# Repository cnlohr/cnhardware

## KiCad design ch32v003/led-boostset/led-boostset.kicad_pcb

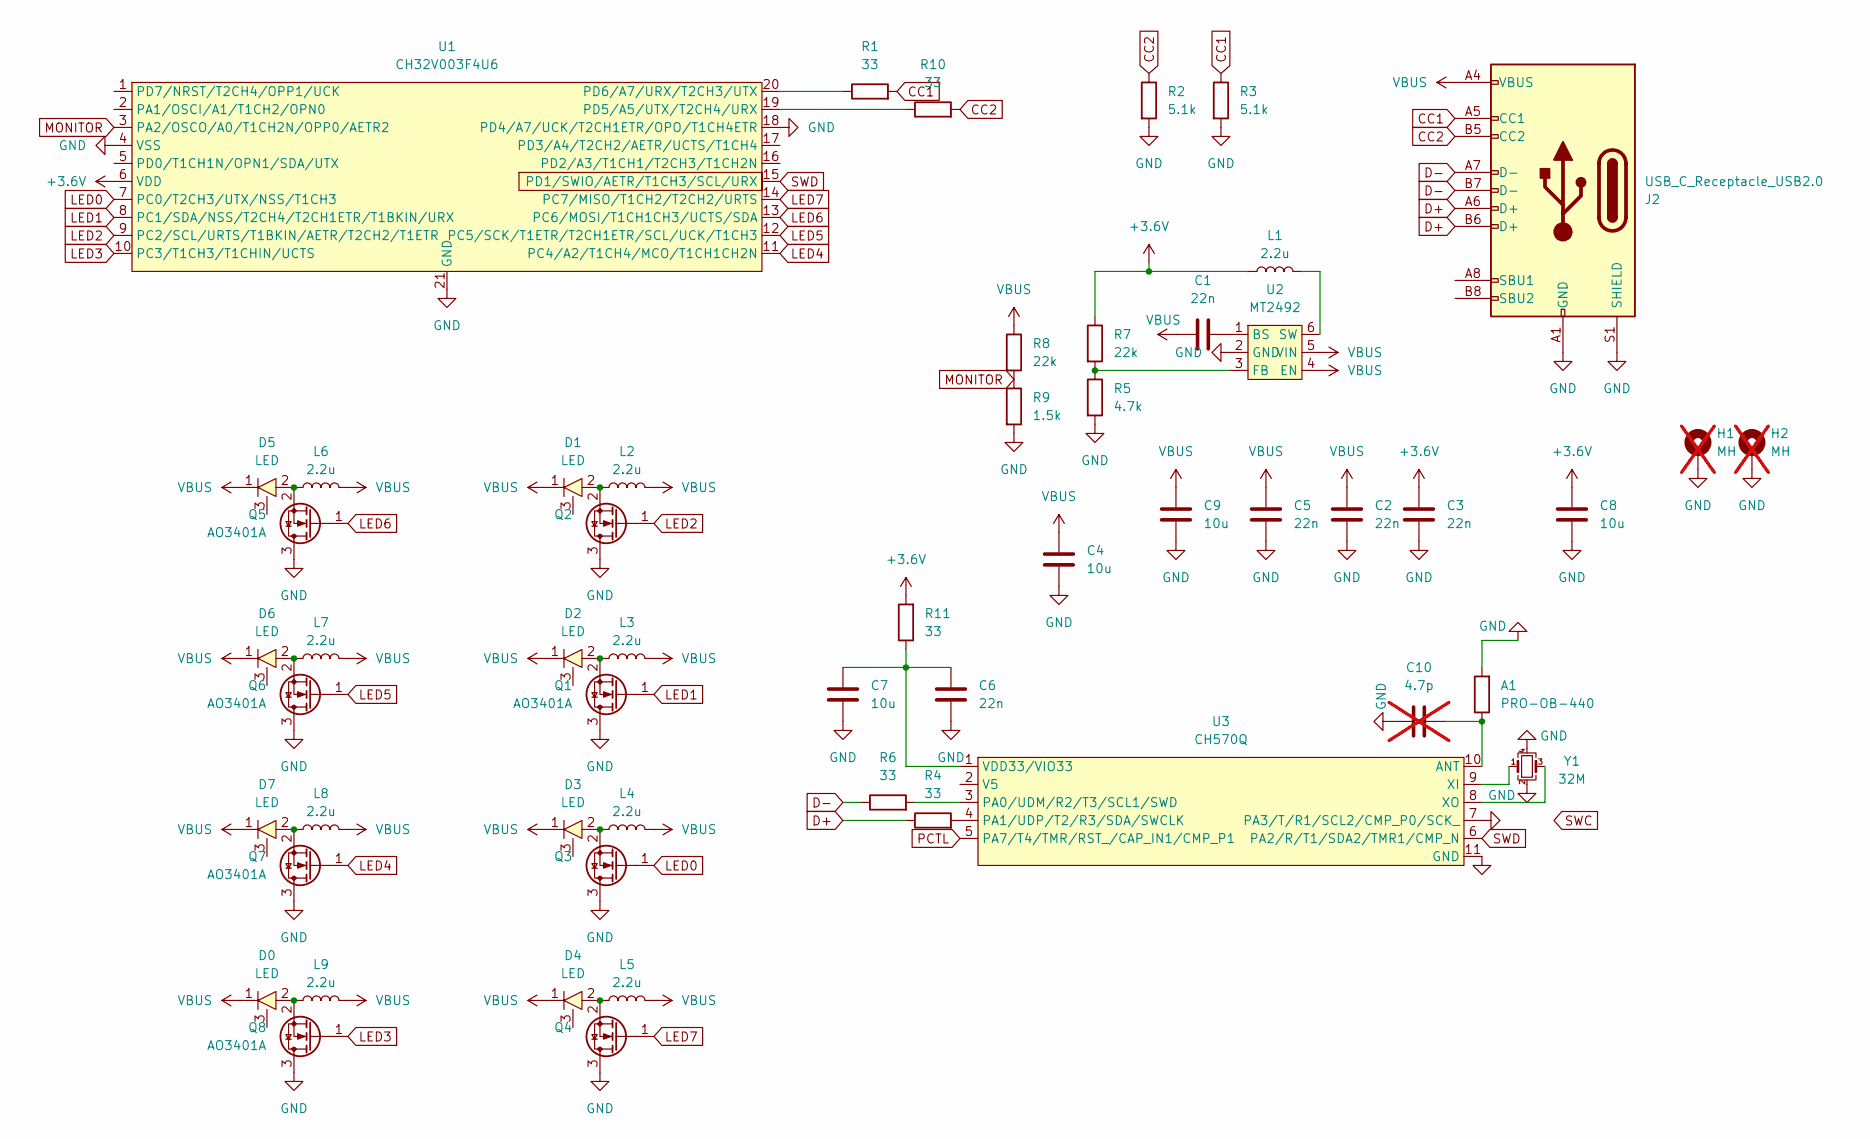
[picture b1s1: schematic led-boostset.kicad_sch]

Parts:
A1: PRO-OB-440; Abracon_PRO-OB-440; LCSC C5122736
C1, C2, C3, C5, C6: 22n; C_0402_1005Metric; LCSC C1532
C4, C7, C8, C9: 10u; C_0805_2012Metric; LCSC C15850
C10: 4.7p; C_0402_1005Metric; not fitted
D0, D1, D2, D3, D4, D5, D6, D7: LED; LED_3535_3W_W_PAD
H1, H2: MH; MountingHole_3.2mm_M3_ISO7380_Pad; not fitted
J2: USB_C_Receptacle_USB2.0; USB_C_SMT_ONLY_Receptacle_USB2.0; LCSC C2927040
L1, L2, L3, L4, L5, L6, L7, L8, L9: 2.2u; L_1008_2520Metric; LCSC C49340356
Q1, Q2, Q3, Q4, Q5, Q6, Q7, Q8: AO3401A; SOT-23; LCSC C15127
R1, R4, R6, R10, R11: 33; R_0603_1608Metric; LCSC C23140
R2, R3: 5.1k; R_0402_1005Metric; LCSC C25905
R5: 4.7k; R_0402_1005Metric; LCSC C25900
R7, R8: 22k; R_0603_1608Metric; LCSC C31850
R9: 1.5k; R_0402_1005Metric; LCSC C25867
U1: CH32V003F4U6; QFN-20-1EP_3x3mm_P0.4mm_EP1.65x1.65mm; LCSC C5299908
U2: MT2492; SOT-23-6; LCSC C89358
U3: CH570Q; DFN-10-1EP_3x3mm_P0.5mm_EP1.7x2.5mm; LCSC C49260680
Y1: 32M; Crystal_SMD_2016-4Pin_2.0x1.6mm; LCSC C718072

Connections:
+3.6V: C3.2, C8.2, L1.1, R7.1, R11.2, U1.6 (VDD)
CC1: J2.A5 (CC1), R1.2, R3.1
CC2: J2.B5 (CC2), R2.1, R10.2
D+: J2.A6 (D+), J2.B6 (D+), R4.1
D-: J2.A7 (D-), J2.B7 (D-), R6.1
GND: A1.2, C2.1, C3.1, C4.1, C5.1, C6.1, C7.1, C8.1, C9.1, C10.2, H1.1, H2.1, J2.A1 (GND), J2.A12 (GND), J2.B1 (GND), J2.B12 (GND), J2.S1 (SHIELD), Q1.3 (D), Q2.3 (D), Q3.3 (D), Q4.3 (D), Q5.3 (D), Q6.3 (D), Q7.3 (D), Q8.3 (D), R2.2, R3.2, R5.2, R9.2, U1.4 (VSS), U1.18 (PD4/A7/UCK/T2CH1ETR/OPO/T1CH4ETR), U1.21 (GND), U2.2 (GND), U3.7 (PA3/T/R1/SCL2/CMP_P0/SCK_), U3.11 (GND), Y1.2, Y1.4
LED0: Q3.1 (G), U1.7 (PC0/T2CH3/UTX/NSS/T1CH3)
LED1: Q1.1 (G), U1.8 (PC1/SDA/NSS/T2CH4/T2CH1ETR/T1BKIN/URX)
LED2: Q2.1 (G), U1.9 (PC2/SCL/URTS/T1BKIN/AETR/T2CH2/T1ETR)
LED3: Q8.1 (G), U1.10 (PC3/T1CH3/T1CHIN/UCTS)
LED4: Q7.1 (G), U1.11 (PC4/A2/T1CH4/MCO/T1CH1CH2N)
LED5: Q6.1 (G), U1.12 (PC5/SCK/T1ETR/T2CH1ETR/SCL/UCK/T1CH3)
LED6: Q5.1 (G), U1.13 (PC6/MOSI/T1CH1CH3/UCTS/SDA)
LED7: Q4.1 (G), U1.14 (PC7/MISO/T1CH2/T2CH2/URTS)
MONITOR: R8.2, R9.1, U1.3 (PA2/OSCO/A0/T1CH2N/OPP0/AETR2)
unnamed: D2.2, L3.1, Q1.2 (S)
unnamed: D1.2, L2.1, Q2.2 (S)
unnamed: D3.2, L4.1, Q3.2 (S)
unnamed: D4.2, L5.1, Q4.2 (S)
unnamed: D5.2, L6.1, Q5.2 (S)
unnamed: D6.2, L7.1, Q6.2 (S)
unnamed: D7.2, L8.1, Q7.2 (S)
unnamed: D0.2, L9.1, Q8.2 (S)
unnamed: R10.1, U1.19 (PD5/A5/UTX/T2CH4/URX)
unnamed: R1.1, U1.20 (PD6/A7/URX/T2CH3/UTX)
unnamed: C1.2, U2.1 (BS)
unnamed: R5.1, R7.2, U2.3 (FB)
unnamed: L1.2, U2.6 (SW)
unnamed: A1.1, C10.1, U3.10 (ANT)
unnamed: R6.2, U3.3 (PA0/UDM/R2/T3/SCL1/SWD)
unnamed: R4.2, U3.4 (PA1/UDP/T2/R3/SDA/SWCLK)
unnamed: C6.2, C7.2, R11.1, U3.1 (VDD33/VIO33)
unnamed: U3.9 (XI), Y1.1
unnamed: U3.8 (XO), Y1.3
PCTL: U3.5 (PA7/T4/TMR/RST_/CAP_IN1/CMP_P1)
SWD: U1.15 (PD1/SWIO/AETR/T1CH3/SCL/URX), U3.6 (PA2/R/T1/SDA2/TMR1/CMP_N)
VBUS: C1.1, C2.2, C4.2, C5.2, C9.2, D0.1, D1.1, D2.1, D3.1, D4.1, D5.1, D6.1, D7.1, J2.A4 (VBUS), J2.A9 (VBUS), J2.B4 (VBUS), J2.B9 (VBUS), L2.2, L3.2, L4.2, L5.2, L6.2, L7.2, L8.2, L9.2, R8.1, U2.4 (EN), U2.5 (VIN)

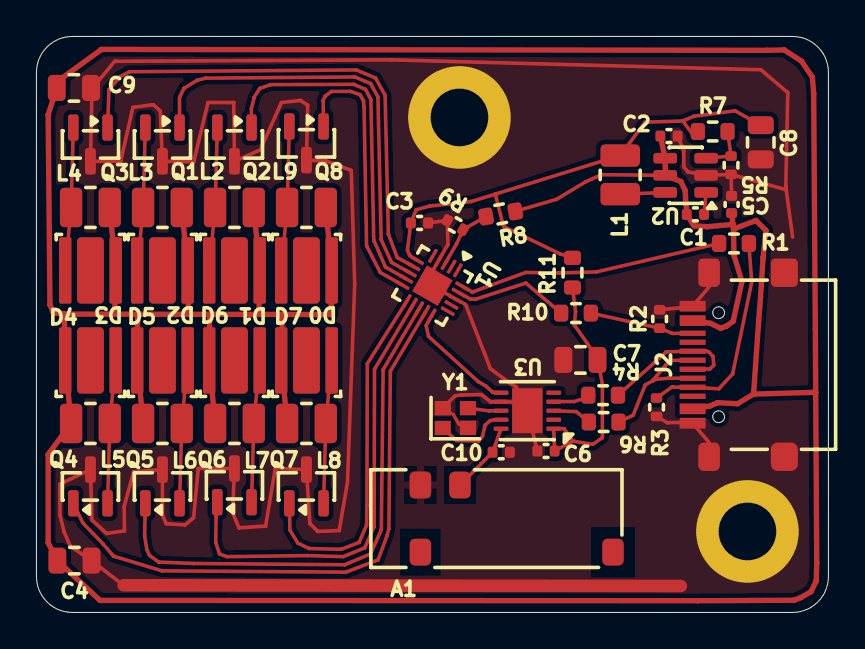
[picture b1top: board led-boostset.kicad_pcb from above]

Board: 2 copper layers, 44.0 x 32.0 mm, 54 parts (0 on the bottom side), 36 nets.

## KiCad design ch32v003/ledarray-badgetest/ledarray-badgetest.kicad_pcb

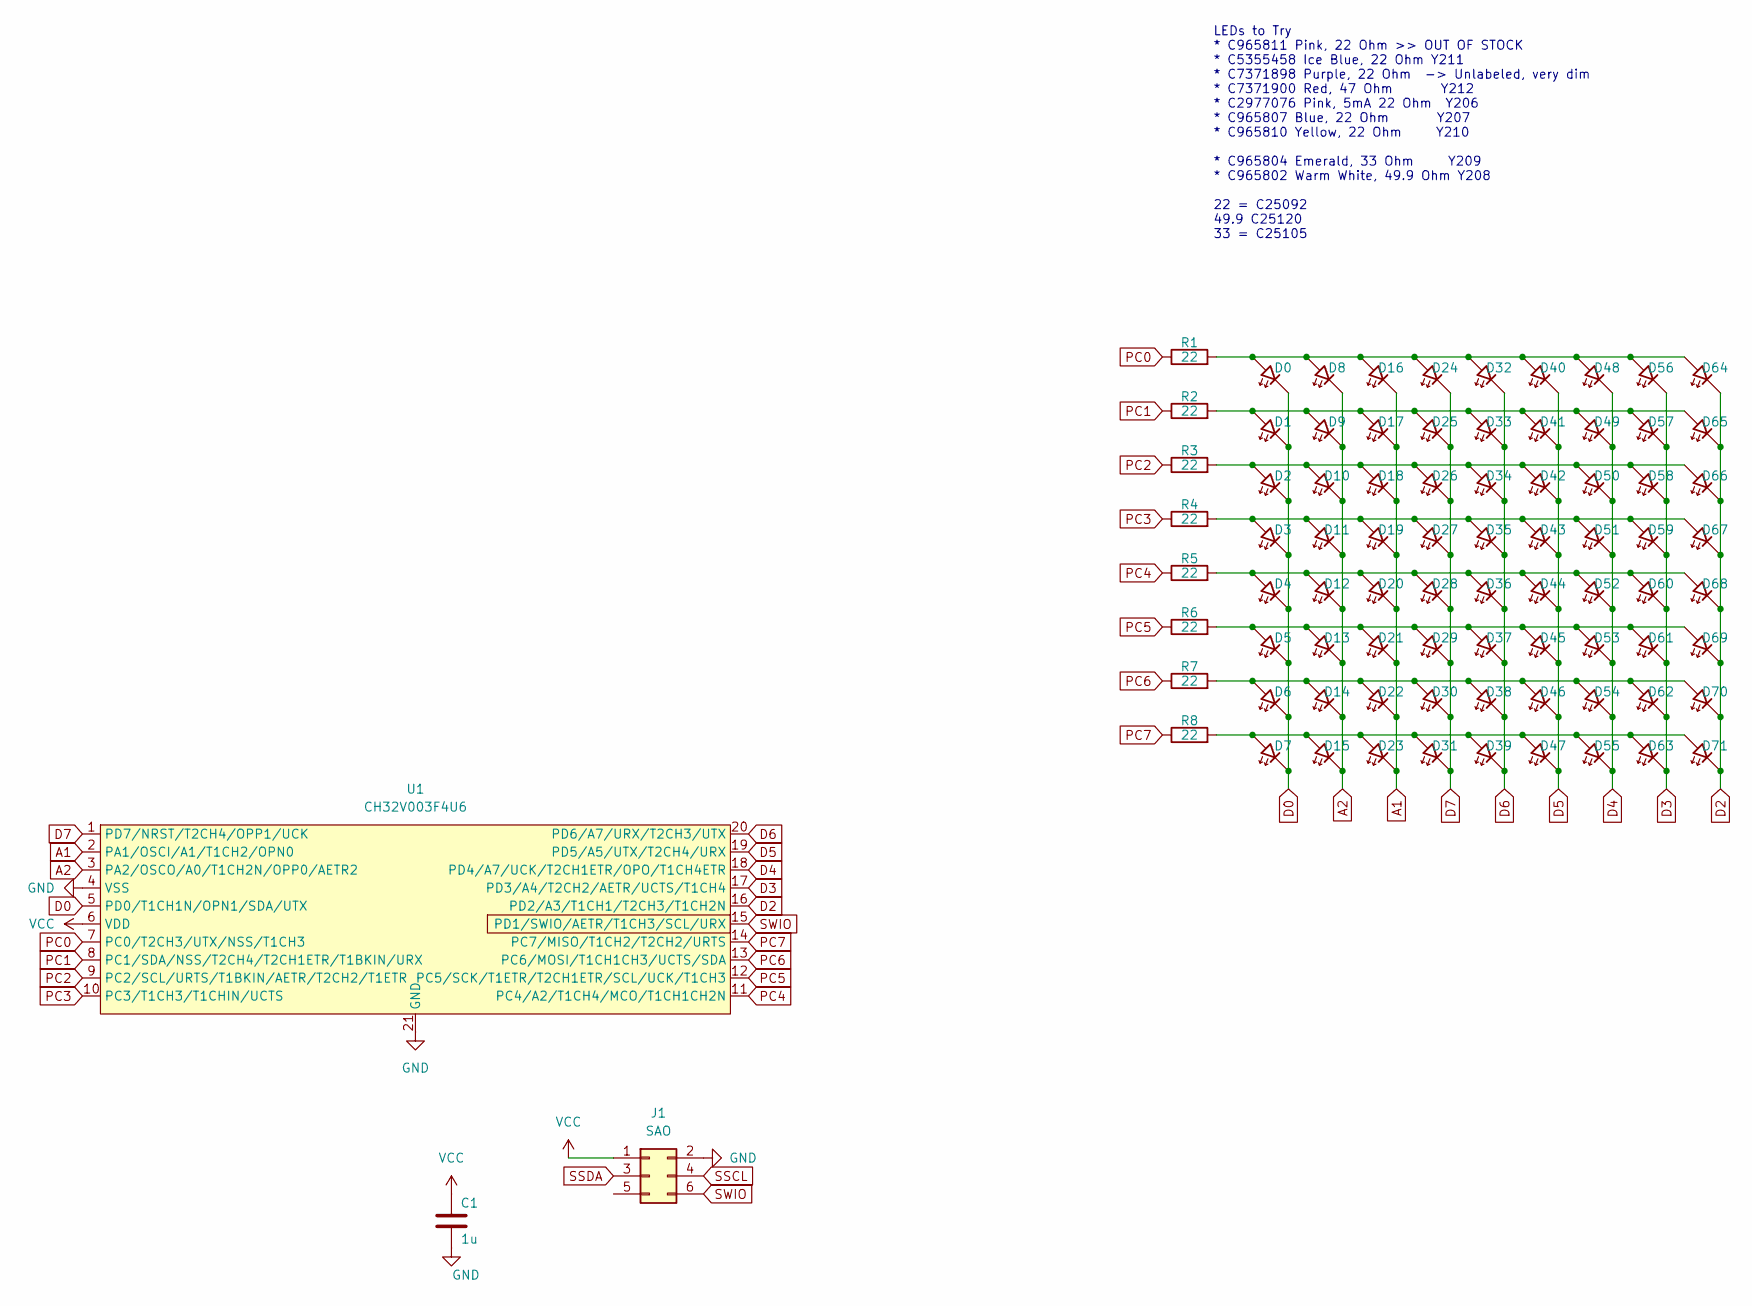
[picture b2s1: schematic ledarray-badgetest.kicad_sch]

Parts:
C1: 1u; R_0402_1005Metric; LCSC C52923
D0, D1, D2, D3, D4, D5, D6, D7, D8, D9, D10, D11, D12, D13, D14, D15, D16, D17, D18, D19, D20, D21, D22, D23, D24, D25, D26, D27, D28, D29, D30, D31, D32, D33, D34, D35, D36, D37, D38, D39, D40, D41, D42, D43, D44, D45, D46, D47, D48, D49, D50, D51, D52, D53, D54, D55, D56, D57, D58, D59, D60, D61, D62, D63, D64, D65, D66, D67, D68, D69, D70, D71: LED_45deg; LED_0603_1608Metric; LCSC C2977076
J1: SAO; PinHeader_2x03_P2.54mm_Vertical_SMD
R1, R2, R3, R4, R5, R6, R7, R8: 22; R_0402_1005Metric; LCSC C25092
U1: CH32V003F4U6; QFN-20-1EP_3x3mm_P0.4mm_EP1.65x1.65mm; LCSC C5299908

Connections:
A1: D16.1 (K), D17.1 (K), D18.1 (K), D19.1 (K), D20.1 (K), D21.1 (K), D22.1 (K), D23.1 (K), U1.2 (PA1/OSCI/A1/T1CH2/OPN0)
A2: D8.1 (K), D9.1 (K), D10.1 (K), D11.1 (K), D12.1 (K), D13.1 (K), D14.1 (K), D15.1 (K), U1.3 (PA2/OSCO/A0/T1CH2N/OPP0/AETR2)
D0: D0.1 (K), D1.1 (K), D2.1 (K), D3.1 (K), D4.1 (K), D5.1 (K), D6.1 (K), D7.1 (K), U1.5 (PD0/T1CH1N/OPN1/SDA/UTX)
D2: D64.1 (K), D65.1 (K), D66.1 (K), D67.1 (K), D68.1 (K), D69.1 (K), D70.1 (K), D71.1 (K), U1.16 (PD2/A3/T1CH1/T2CH3/T1CH2N)
D3: D56.1 (K), D57.1 (K), D58.1 (K), D59.1 (K), D60.1 (K), D61.1 (K), D62.1 (K), D63.1 (K), U1.17 (PD3/A4/T2CH2/AETR/UCTS/T1CH4)
D4: D48.1 (K), D49.1 (K), D50.1 (K), D51.1 (K), D52.1 (K), D53.1 (K), D54.1 (K), D55.1 (K), U1.18 (PD4/A7/UCK/T2CH1ETR/OPO/T1CH4ETR)
D5: D40.1 (K), D41.1 (K), D42.1 (K), D43.1 (K), D44.1 (K), D45.1 (K), D46.1 (K), D47.1 (K), U1.19 (PD5/A5/UTX/T2CH4/URX)
D6: D32.1 (K), D33.1 (K), D34.1 (K), D35.1 (K), D36.1 (K), D37.1 (K), D38.1 (K), D39.1 (K), U1.20 (PD6/A7/URX/T2CH3/UTX)
D7: D24.1 (K), D25.1 (K), D26.1 (K), D27.1 (K), D28.1 (K), D29.1 (K), D30.1 (K), D31.1 (K), U1.1 (PD7/NRST/T2CH4/OPP1/UCK)
GND: C1.1, J1.2, U1.4 (VSS), U1.21 (GND)
unnamed: D0.2 (A), D8.2 (A), D16.2 (A), D24.2 (A), D32.2 (A), D40.2 (A), D48.2 (A), D56.2 (A), D64.2 (A), R1.2
unnamed: D1.2 (A), D9.2 (A), D17.2 (A), D25.2 (A), D33.2 (A), D41.2 (A), D49.2 (A), D57.2 (A), D65.2 (A), R2.2
unnamed: D2.2 (A), D10.2 (A), D18.2 (A), D26.2 (A), D34.2 (A), D42.2 (A), D50.2 (A), D58.2 (A), D66.2 (A), R3.2
unnamed: D3.2 (A), D11.2 (A), D19.2 (A), D27.2 (A), D35.2 (A), D43.2 (A), D51.2 (A), D59.2 (A), D67.2 (A), R4.2
unnamed: D4.2 (A), D12.2 (A), D20.2 (A), D28.2 (A), D36.2 (A), D44.2 (A), D52.2 (A), D60.2 (A), D68.2 (A), R5.2
unnamed: D5.2 (A), D13.2 (A), D21.2 (A), D29.2 (A), D37.2 (A), D45.2 (A), D53.2 (A), D61.2 (A), D69.2 (A), R6.2
unnamed: D6.2 (A), D14.2 (A), D22.2 (A), D30.2 (A), D38.2 (A), D46.2 (A), D54.2 (A), D62.2 (A), D70.2 (A), R7.2
unnamed: D7.2 (A), D15.2 (A), D23.2 (A), D31.2 (A), D39.2 (A), D47.2 (A), D55.2 (A), D63.2 (A), D71.2 (A), R8.2
PC0: R1.1, U1.7 (PC0/T2CH3/UTX/NSS/T1CH3)
PC1: R2.1, U1.8 (PC1/SDA/NSS/T2CH4/T2CH1ETR/T1BKIN/URX)
PC2: R3.1, U1.9 (PC2/SCL/URTS/T1BKIN/AETR/T2CH2/T1ETR)
PC3: R4.1, U1.10 (PC3/T1CH3/T1CHIN/UCTS)
PC4: R5.1, U1.11 (PC4/A2/T1CH4/MCO/T1CH1CH2N)
PC5: R6.1, U1.12 (PC5/SCK/T1ETR/T2CH1ETR/SCL/UCK/T1CH3)
PC6: R7.1, U1.13 (PC6/MOSI/T1CH1CH3/UCTS/SDA)
PC7: R8.1, U1.14 (PC7/MISO/T1CH2/T2CH2/URTS)
SSCL: J1.4
SSDA: J1.3
SWIO: J1.6, U1.15 (PD1/SWIO/AETR/T1CH3/SCL/URX)
VCC: C1.2, J1.1, U1.6 (VDD)

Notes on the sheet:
LEDs to Try * C965811 Pink, 22 Ohm >> OUT OF STOCK * C5355458 Ice Blue, 22 Ohm Y211 * C7371898 Purple, 22 Ohm -> Unlabeled, very dim * C7371900 Red, 47 Ohm Y212 * C2977076 Pink, 5mA 22 Ohm Y206 * C965807 Blue, 22 Ohm Y207 * C965810 Yellow, 22 Ohm Y210 * C965804 Emerald, 33 Ohm Y209 * C965802 Warm W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

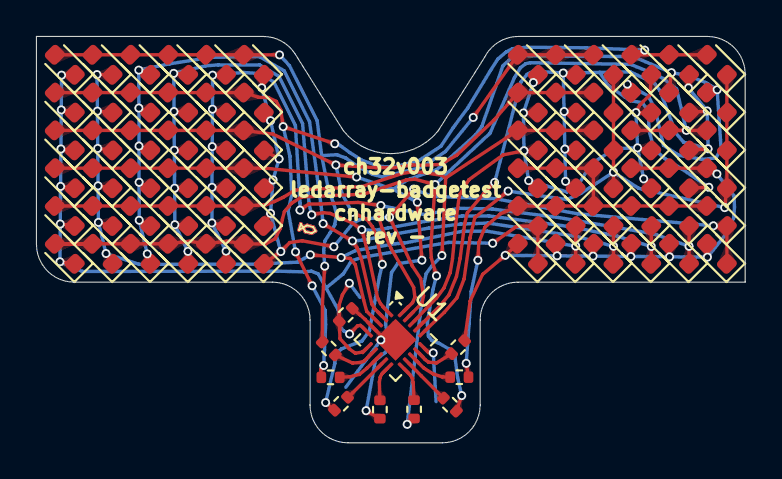
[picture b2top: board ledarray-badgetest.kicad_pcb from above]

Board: 2 copper layers, 39.4 x 22.6 mm, 83 parts (1 on the bottom side), 28 nets.

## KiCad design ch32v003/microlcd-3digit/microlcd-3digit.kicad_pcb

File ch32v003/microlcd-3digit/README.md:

THIS HAS MOVED HERE:
https://github.com/cnlohr/ch32v003_3digit_lcd_usb/

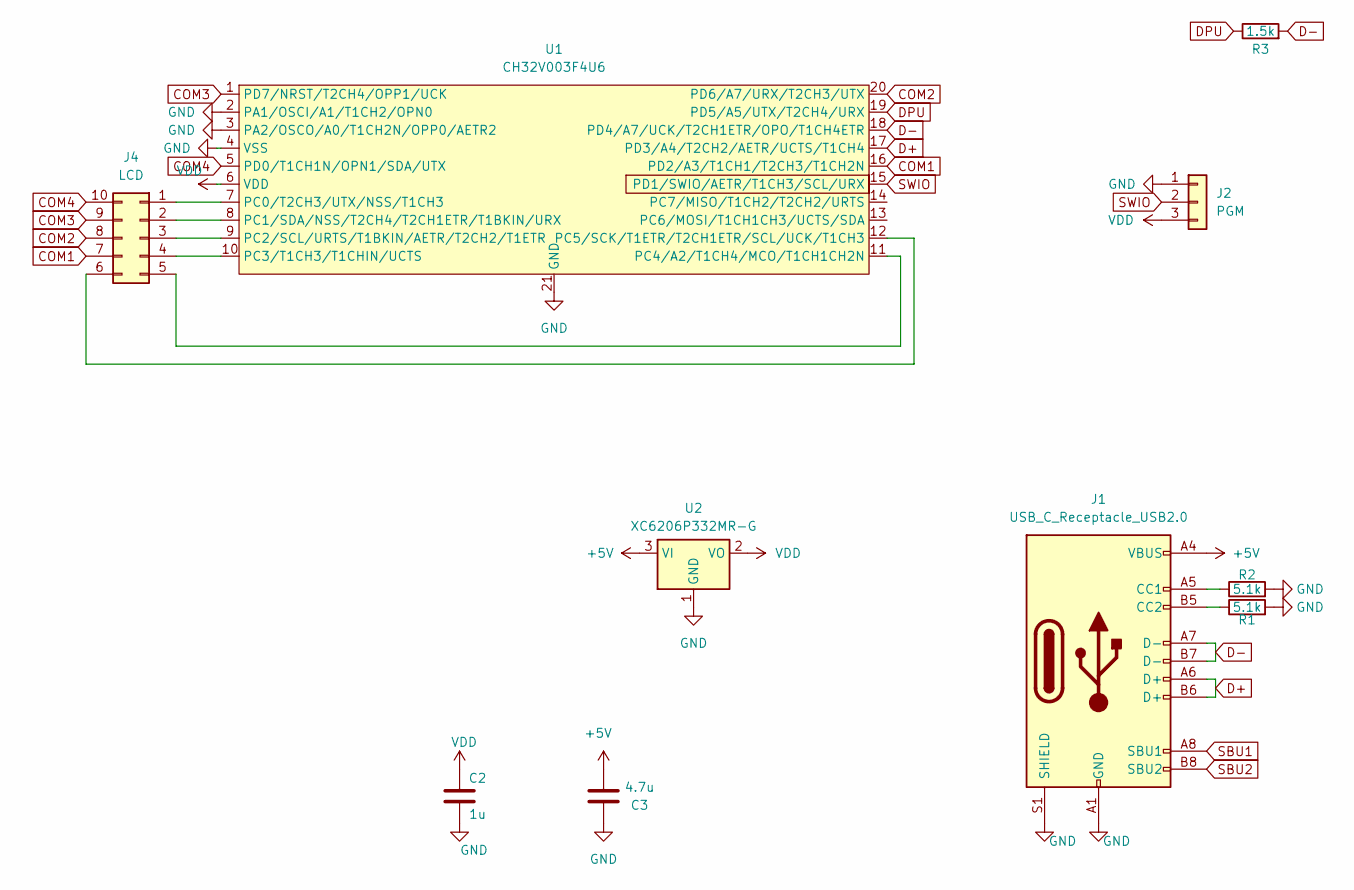
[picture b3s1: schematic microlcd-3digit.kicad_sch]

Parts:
C2: 1u; R_0402_1005Metric; LCSC C52923
C3: 4.7u; R_0402_1005Metric; LCSC C368809
J1: USB_C_Receptacle_USB2.0; USB_C_PADDLE
J2: PGM; PinHeader_1x03_P2.54mm_Vertical
J4: LCD; TINY_LCD_3_DIGIT
R1, R2: 5.1k; R_0402_1005Metric; LCSC C25905
R3: 1.5k; R_0402_1005Metric; LCSC C25867
U1: CH32V003F4U6; QFN-20-1EP_3x3mm_P0.4mm_EP1.65x1.65mm; LCSC C5299908
U2: XC6206P332MR-G; SOT-23; LCSC C5446

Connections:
+5V: C3.2, J1.A4 (VBUS), J1.A9 (VBUS), J1.B4 (VBUS), J1.B9 (VBUS), U2.3 (VI)
COM1: J4.7, U1.16 (PD2/A3/T1CH1/T2CH3/T1CH2N)
COM2: J4.8, U1.20 (PD6/A7/URX/T2CH3/UTX)
COM3: J4.9, U1.1 (PD7/NRST/T2CH4/OPP1/UCK)
COM4: J4.10, U1.5 (PD0/T1CH1N/OPN1/SDA/UTX)
D+: J1.A6 (D+), J1.B6 (D+), U1.17 (PD3/A4/T2CH2/AETR/UCTS/T1CH4)
D-: J1.A7 (D-), J1.B7 (D-), R3.2, U1.18 (PD4/A7/UCK/T2CH1ETR/OPO/T1CH4ETR)
DPU: R3.1, U1.19 (PD5/A5/UTX/T2CH4/URX)
GND: C2.1, C3.1, J1.A1 (GND), J1.A12 (GND), J1.B1 (GND), J1.B12 (GND), J1.S1 (SHIELD), J2.1, R1.2, R2.2, U1.2 (PA1/OSCI/A1/T1CH2/OPN0), U1.3 (PA2/OSCO/A0/T1CH2N/OPP0/AETR2), U1.4 (VSS), U1.21 (GND), U2.1 (GND)
unnamed: J1.A5 (CC1), R2.1
unnamed: J1.B5 (CC2), R1.1
unnamed: J4.1, U1.7 (PC0/T2CH3/UTX/NSS/T1CH3)
unnamed: J4.2, U1.8 (PC1/SDA/NSS/T2CH4/T2CH1ETR/T1BKIN/URX)
unnamed: J4.3, U1.9 (PC2/SCL/URTS/T1BKIN/AETR/T2CH2/T1ETR)
unnamed: J4.4, U1.10 (PC3/T1CH3/T1CHIN/UCTS)
unnamed: J4.5, U1.11 (PC4/A2/T1CH4/MCO/T1CH1CH2N)
unnamed: J4.6, U1.12 (PC5/SCK/T1ETR/T2CH1ETR/SCL/UCK/T1CH3)
SBU1: J1.A8 (SBU1)
SBU2: J1.B8 (SBU2)
SWIO: J2.2, U1.15 (PD1/SWIO/AETR/T1CH3/SCL/URX)
VDD: C2.2, J2.3, U1.6 (VDD), U2.2 (VO)

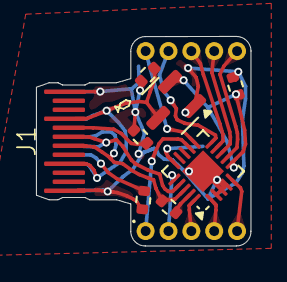
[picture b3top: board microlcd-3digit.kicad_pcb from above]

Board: 2 copper layers, 11.9 x 11.6 mm, 10 parts (1 on the bottom side), 19 nets.

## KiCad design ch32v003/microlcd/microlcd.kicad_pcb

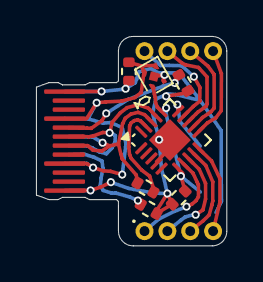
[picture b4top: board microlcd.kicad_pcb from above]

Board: 2 copper layers, 10.6 x 11.6 mm, 10 parts (1 on the bottom side), 17 nets.

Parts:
C2: 1u; R_0402_1005Metric
C3: 4.7u; R_0402_1005Metric
J1: USB_C_Receptacle_USB2.0; USB_C_PADDLE
J2: PGM; PinHeader_1x03_P2.54mm_Vertical
J3: LCD; TINY_LCD_2_DIGIT
R1, R2: 5.1k; R_0402_1005Metric
R3: 1.5k; R_0402_1005Metric
U1: CH32V003F4U6; QFN-20-1EP_3x3mm_P0.4mm_EP1.65x1.65mm
U3: 3.3vReg; xdfn-reg

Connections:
+5V: C3.2, J1.A4 (VBUS), J1.A9 (VBUS), J1.B4 (VBUS), J1.B9 (VBUS), U3.3 (EN), U3.4 (IN)
COM1: J3.5, U1.11 (PC4/A2/T1CH4/MCO/T1CH1CH2N)
COM2: J3.6, U1.12 (PC5/SCK/T1ETR/T2CH1ETR/SCL/UCK/T1CH3)
COM3: J3.7, U1.13 (PC6/MOSI/T1CH1CH3/UCTS/SDA)
COM4: J3.8, U1.14 (PC7/MISO/T1CH2/T2CH2/URTS)
D+: J1.A6 (D+), J1.B6 (D+), U1.17 (PD3/A4/T2CH2/AETR/UCTS/T1CH4)
D-: J1.A7 (D-), J1.B7 (D-), R3.2, U1.18 (PD4/A7/UCK/T2CH1ETR/OPO/T1CH4ETR)
DPU: R3.1, U1.19 (PD5/A5/UTX/T2CH4/URX)
GND: C2.1, C3.1, J1.A1 (GND), J1.A12 (GND), J1.B1 (GND), J1.B12 (GND), J2.1, R1.2, R2.2, U1.4 (VSS), U1.21 (GND), U3.2 (GND), U3.5 (GND)
unnamed: J1.A5 (CC1), R2.1
unnamed: J1.B5 (CC2), R1.1
unnamed: J3.1, U1.7 (PC0/T2CH3/UTX/NSS/T1CH3)
unnamed: J3.2, U1.8 (PC1/SDA/NSS/T2CH4/T2CH1ETR/T1BKIN/URX)
unnamed: J3.3, U1.9 (PC2/SCL/URTS/T1BKIN/AETR/T2CH2/T1ETR)
unnamed: J3.4, U1.10 (PC3/T1CH3/T1CHIN/UCTS)
SWIO: J2.2, U1.15 (PD1/SWIO/AETR/T1CH3/SCL/URX)
VDD: C2.2, J2.3, U1.6 (VDD), U1.16 (PD2/A3/T1CH1/T2CH3/T1CH2N), U3.1 (OUT)

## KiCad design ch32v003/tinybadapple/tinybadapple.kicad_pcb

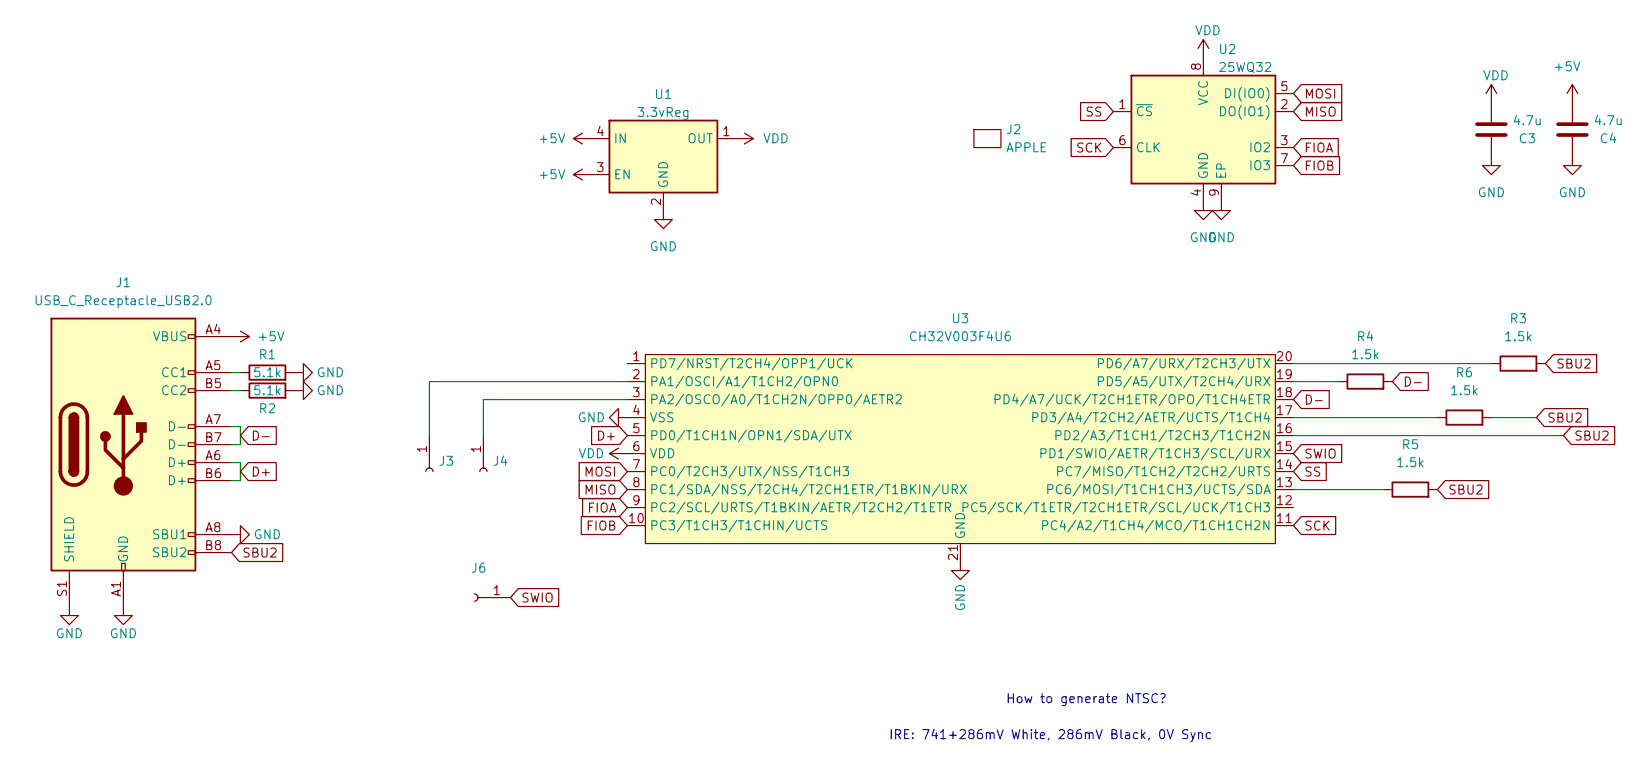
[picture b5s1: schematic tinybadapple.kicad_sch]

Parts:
C3, C4: 4.7u; R_0402_1005Metric; LCSC C368809
J1: USB_C_Receptacle_USB2.0; USB_C_MOD_Receptacle_HRO_TYPE-C-31-M-12; LCSC C2765186
J2: APPLE; apple
J3, J4, J6: TestPoint_Pad_1.0x1.0mm
R1, R2: 5.1k; R_0402_1005Metric; LCSC C25905
R3, R4, R5, R6: 1.5k; R_0402_1005Metric; LCSC C25867
U1: 3.3vReg; xdfn-reg; LCSC C379350
U2: 25WQ32; USON8-LINE(2x3); LCSC C5258281
U3: CH32V003F4U6; QFN-20-1EP_3x3mm_P0.4mm_EP1.65x1.65mm; LCSC C5299908

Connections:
+5V: C4.2, J1.A4 (VBUS), J1.A9 (VBUS), J1.B4 (VBUS), J1.B9 (VBUS), U1.3 (EN), U1.4 (IN)
D+: J1.A6 (D+), J1.B6 (D+), U3.5 (PD0/T1CH1N/OPN1/SDA/UTX)
D-: J1.A7 (D-), J1.B7 (D-), R4.2, U3.18 (PD4/A7/UCK/T2CH1ETR/OPO/T1CH4ETR)
FIOA: U2.3 (IO2), U3.9 (PC2/SCL/URTS/T1BKIN/AETR/T2CH2/T1ETR)
FIOB: U2.7 (IO3), U3.10 (PC3/T1CH3/T1CHIN/UCTS)
GND: C3.1, C4.1, J1.A1 (GND), J1.A8 (SBU1), J1.A12 (GND), J1.B1 (GND), J1.B12 (GND), J1.S1 (SHIELD), R1.2, R2.2, U1.2 (GND), U1.5 (GND), U2.4 (GND), U2.9 (EP), U3.4 (VSS), U3.21 (GND)
MISO: U2.2 (DO(IO1)), U3.8 (PC1/SDA/NSS/T2CH4/T2CH1ETR/T1BKIN/URX)
MOSI: U2.5 (DI(IO0)), U3.7 (PC0/T2CH3/UTX/NSS/T1CH3)
unnamed: J1.A5 (CC1), R1.1
unnamed: J1.B5 (CC2), R2.1
unnamed: J3.1, U3.2 (PA1/OSCI/A1/T1CH2/OPN0)
unnamed: J4.1, U3.3 (PA2/OSCO/A0/T1CH2N/OPP0/AETR2)
unnamed: R5.1, U3.13 (PC6/MOSI/T1CH1CH3/UCTS/SDA)
unnamed: R6.1, U3.17 (PD3/A4/T2CH2/AETR/UCTS/T1CH4)
unnamed: R4.1, U3.19 (PD5/A5/UTX/T2CH4/URX)
unnamed: R3.1, U3.20 (PD6/A7/URX/T2CH3/UTX)
SBU2: J1.B8 (SBU2), R3.2, R5.2, R6.2, U3.16 (PD2/A3/T1CH1/T2CH3/T1CH2N)
SCK: U2.6 (CLK), U3.11 (PC4/A2/T1CH4/MCO/T1CH1CH2N)
SS: U2.1 (~CS), U3.14 (PC7/MISO/T1CH2/T2CH2/URTS)
SWIO: J6.1, U3.15 (PD1/SWIO/AETR/T1CH3/SCL/URX)
VDD: C3.2, U1.1 (OUT), U2.8 (VCC), U3.6 (VDD)

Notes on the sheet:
How to generate NTSC?
IRE: 741+286mV White, 286mV Black, 0V Sync

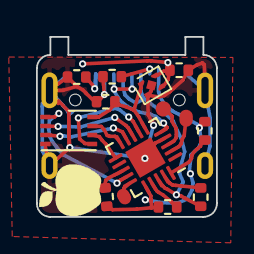
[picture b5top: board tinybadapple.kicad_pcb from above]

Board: 2 copper layers, 10.0 x 10.0 mm, 16 parts (1 on the bottom side), 21 nets.

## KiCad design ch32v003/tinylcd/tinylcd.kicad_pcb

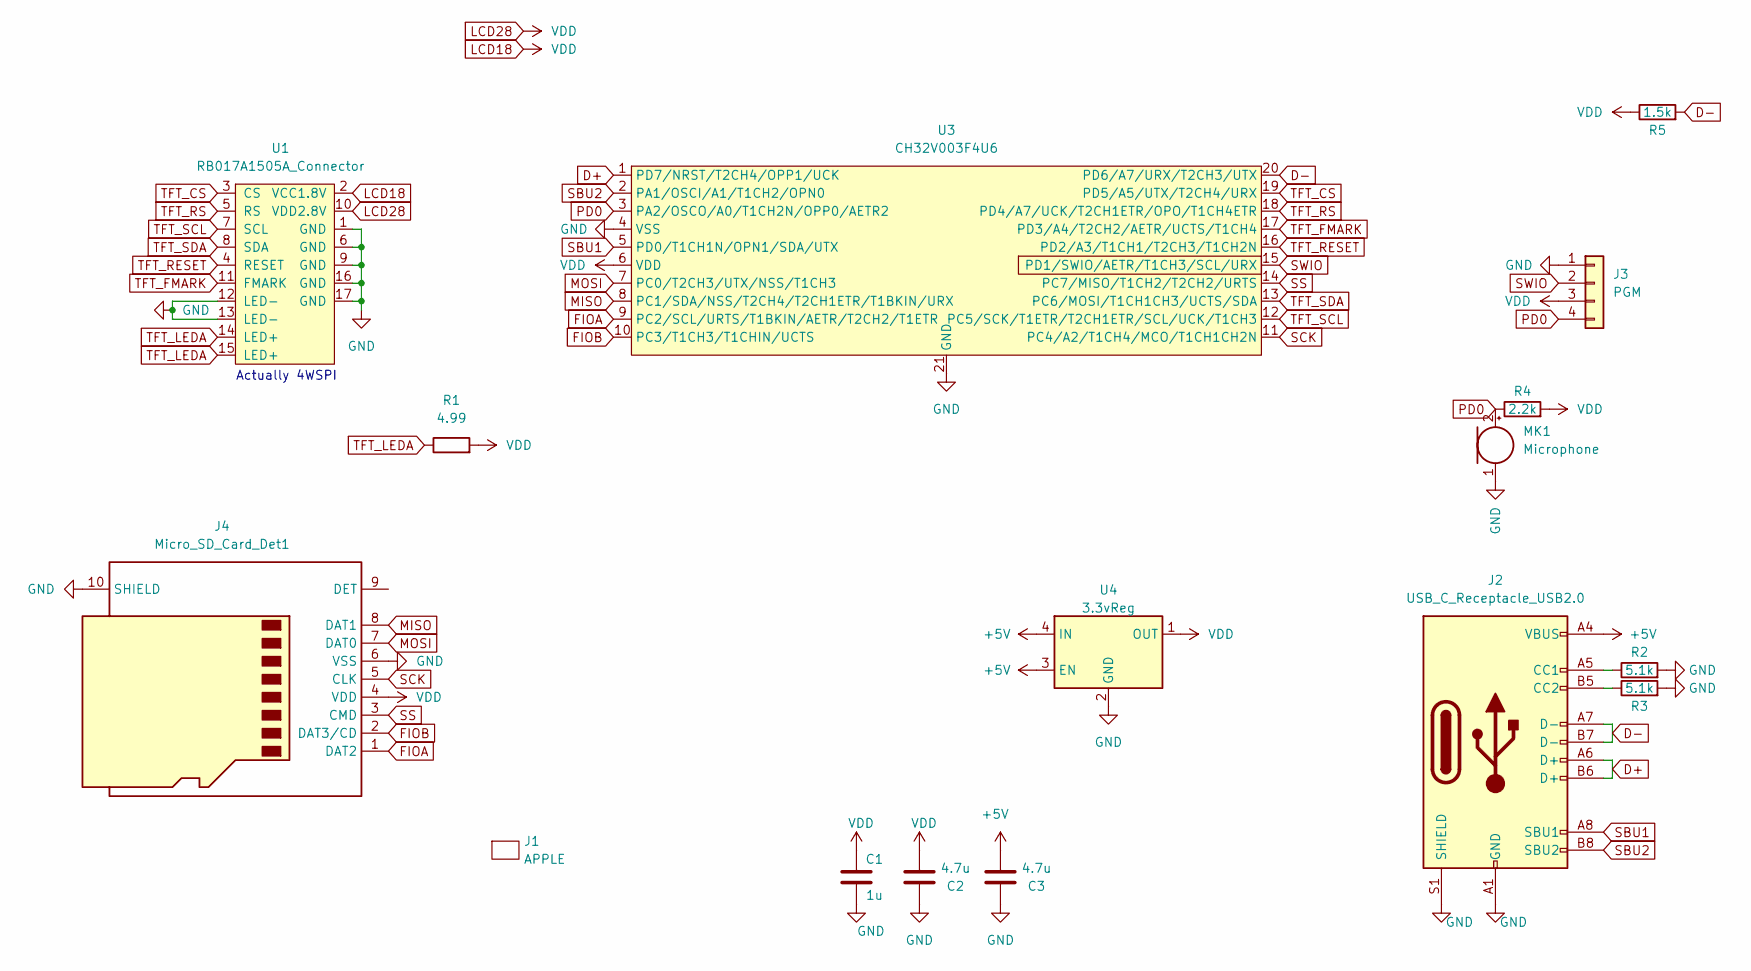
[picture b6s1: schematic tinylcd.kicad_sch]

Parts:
C1: 1u; R_0402_1005Metric; LCSC C52923
C2, C3: 4.7u; R_0402_1005Metric; LCSC C368809
J1: APPLE; apple
J2: USB_C_Receptacle_USB2.0; USB_C_Receptacle_HRO_TYPE-C-31-M-12; LCSC C2765186
J3: PGM; PinHeader_1x04_P2.54mm_Vertical; LCSC NP
J4: Micro_SD_Card_Det1; MicroSD-C393941-SHOU-HAN-TF-PUSH; LCSC C393941
MK1: Microphone; GOERTEK_MIC_B4013AM423; LCSC C529872
R1: 4.99; R_0603_1608Metric; LCSC C103684
R2, R3: 5.1k; R_0402_1005Metric; LCSC C25905
R4: 2.2k; R_0402_1005Metric; LCSC C25933
R5: 1.5k; R_0402_1005Metric; LCSC C25867
U1: RB017A1505A_Connector; FLEX15-0.3-HC-FPC-03-10-15RLTAG; LCSC C711418
U3: CH32V003F4U6; QFN-20-1EP_3x3mm_P0.4mm_EP1.65x1.65mm; LCSC C5299908
U4: 3.3vReg; xdfn-reg; LCSC C379350

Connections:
+5V: C3.2, J2.A4 (VBUS), J2.A9 (VBUS), J2.B4 (VBUS), J2.B9 (VBUS), U4.3 (EN), U4.4 (IN)
D+: J2.A6 (D+), J2.B6 (D+), U3.1 (PD7/NRST/T2CH4/OPP1/UCK)
D-: J2.A7 (D-), J2.B7 (D-), R5.2, U3.20 (PD6/A7/URX/T2CH3/UTX)
FIOA: J4.1 (DAT2), U3.9 (PC2/SCL/URTS/T1BKIN/AETR/T2CH2/T1ETR)
FIOB: J4.2 (DAT3/CD), U3.10 (PC3/T1CH3/T1CHIN/UCTS)
GND: C1.1, C2.1, C3.1, J2.A1 (GND), J2.A12 (GND), J2.B1 (GND), J2.B12 (GND), J2.S1 (SHIELD), J3.1, J4.6 (VSS), J4.10 (SHIELD), MK1.1 (-), R2.2, R3.2, U1.1 (GND), U1.6 (GND), U1.9 (GND), U1.12 (LED-), U1.13 (LED-), U1.16 (GND), U1.17 (GND), U3.4 (VSS), U3.21 (GND), U4.2 (GND), U4.5 (GND)
LCD18: C1.2, C2.2, J3.3, J4.4 (VDD), R1.2, R4.2, R5.1, U1.2 (VCC1.8V), U1.10 (VDD2.8V), U3.6 (VDD), U4.1 (OUT)
MISO: J4.8 (DAT1), U3.8 (PC1/SDA/NSS/T2CH4/T2CH1ETR/T1BKIN/URX)
MOSI: J4.7 (DAT0), U3.7 (PC0/T2CH3/UTX/NSS/T1CH3)
unnamed: J2.A5 (CC1), R2.1
unnamed: J2.B5 (CC2), R3.1
PD0: J3.4, MK1.2 (+), R4.1, U3.3 (PA2/OSCO/A0/T1CH2N/OPP0/AETR2)
SBU1: J2.A8 (SBU1), U3.5 (PD0/T1CH1N/OPN1/SDA/UTX)
SBU2: J2.B8 (SBU2), U3.2 (PA1/OSCI/A1/T1CH2/OPN0)
SCK: J4.5 (CLK), U3.11 (PC4/A2/T1CH4/MCO/T1CH1CH2N)
SS: J4.3 (CMD), U3.14 (PC7/MISO/T1CH2/T2CH2/URTS)
SWIO: J3.2, U3.15 (PD1/SWIO/AETR/T1CH3/SCL/URX)
TFT_CS: U1.3 (CS), U3.19 (PD5/A5/UTX/T2CH4/URX)
TFT_FMARK: U1.11 (FMARK), U3.17 (PD3/A4/T2CH2/AETR/UCTS/T1CH4)
TFT_LEDA: R1.1, U1.14 (LED+), U1.15 (LED+)
TFT_RESET: U1.4 (RESET), U3.16 (PD2/A3/T1CH1/T2CH3/T1CH2N)
TFT_RS: U1.5 (RS), U3.18 (PD4/A7/UCK/T2CH1ETR/OPO/T1CH4ETR)
TFT_SCL: U1.7 (SCL), U3.12 (PC5/SCK/T1ETR/T2CH1ETR/SCL/UCK/T1CH3)
TFT_SDA: U1.8 (SDA), U3.13 (PC6/MOSI/T1CH1CH3/UCTS/SDA)

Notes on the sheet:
Actually 4WSPI

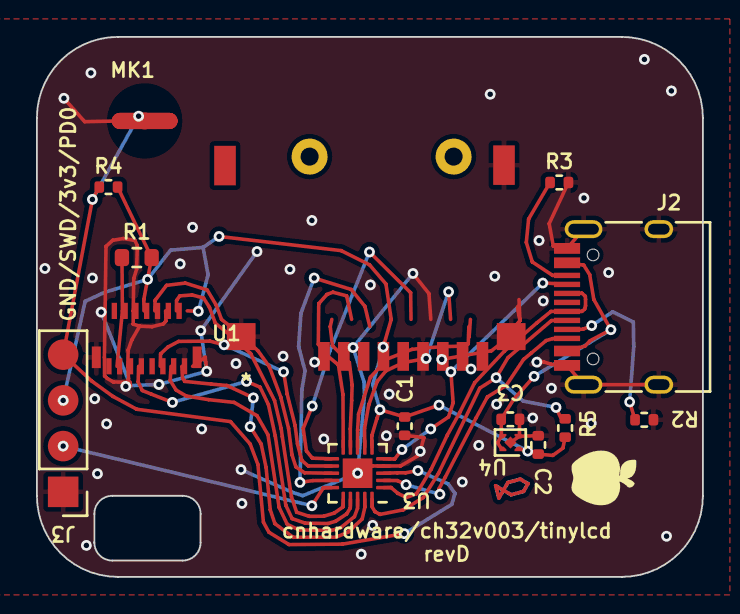
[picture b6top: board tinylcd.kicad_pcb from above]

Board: 2 copper layers, 37.0 x 30.0 mm, 16 parts (0 on the bottom side), 24 nets.

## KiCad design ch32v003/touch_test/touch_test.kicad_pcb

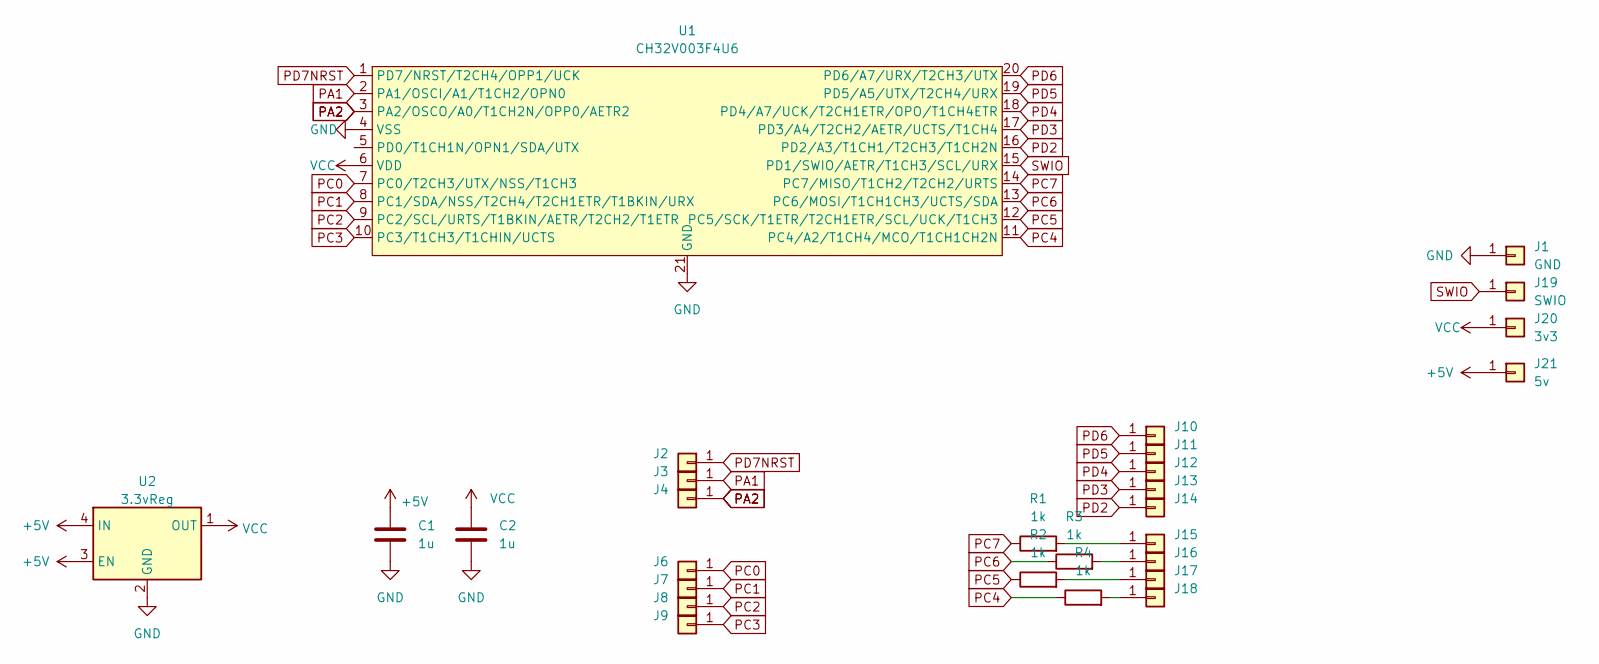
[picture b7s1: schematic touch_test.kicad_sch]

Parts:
C1, C2: 1u; C_0402_1005Metric; LCSC C237173
J1: GND; TestPoint_Pad_1.5x1.5mm
J2, J3, J4, J6, J7, J8, J9, J10, J11, J12, J13, J14, J15, J16, J17, J18: touchpad_10x6.5mm_retircle
J19: SWIO; TestPoint_Pad_1.5x1.5mm
J20: 3v3; TestPoint_Pad_1.5x1.5mm
J21: 5v; TestPoint_Pad_1.5x1.5mm
R1, R2, R3, R4: 1k; R_0402_1005Metric; LCSC C25076
U1: CH32V003F4U6; QFN-20-1EP_3x3mm_P0.4mm_EP1.65x1.65mm; LCSC C5299908
U2: 3.3vReg; xdfn-reg; LCSC C81114

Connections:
+5V: C1.1, J21.1, U2.3 (EN), U2.4 (IN)
GND: C1.2, C2.2, J1.1, U1.4 (VSS), U1.21 (GND), U2.2 (GND), U2.5 (GND)
unnamed: J15.1, R1.2
unnamed: J16.1, R3.2
unnamed: J17.1, R2.2
unnamed: J18.1, R4.2
PA1: J3.1, U1.2 (PA1/OSCI/A1/T1CH2/OPN0)
PA2: J4.1, U1.3 (PA2/OSCO/A0/T1CH2N/OPP0/AETR2)
PC0: J6.1, U1.7 (PC0/T2CH3/UTX/NSS/T1CH3)
PC1: J7.1, U1.8 (PC1/SDA/NSS/T2CH4/T2CH1ETR/T1BKIN/URX)
PC2: J8.1, U1.9 (PC2/SCL/URTS/T1BKIN/AETR/T2CH2/T1ETR)
PC3: J9.1, U1.10 (PC3/T1CH3/T1CHIN/UCTS)
PC4: R4.1, U1.11 (PC4/A2/T1CH4/MCO/T1CH1CH2N)
PC5: R2.1, U1.12 (PC5/SCK/T1ETR/T2CH1ETR/SCL/UCK/T1CH3)
PC6: R3.1, U1.13 (PC6/MOSI/T1CH1CH3/UCTS/SDA)
PC7: R1.1, U1.14 (PC7/MISO/T1CH2/T2CH2/URTS)
PD2: J14.1, U1.16 (PD2/A3/T1CH1/T2CH3/T1CH2N)
PD3: J13.1, U1.17 (PD3/A4/T2CH2/AETR/UCTS/T1CH4)
PD4: J12.1, U1.18 (PD4/A7/UCK/T2CH1ETR/OPO/T1CH4ETR)
PD5: J11.1, U1.19 (PD5/A5/UTX/T2CH4/URX)
PD6: J10.1, U1.20 (PD6/A7/URX/T2CH3/UTX)
PD7NRST: J2.1, U1.1 (PD7/NRST/T2CH4/OPP1/UCK)
SWIO: J19.1, U1.15 (PD1/SWIO/AETR/T1CH3/SCL/URX)
VCC: C2.1, J20.1, U1.6 (VDD), U2.1 (OUT)

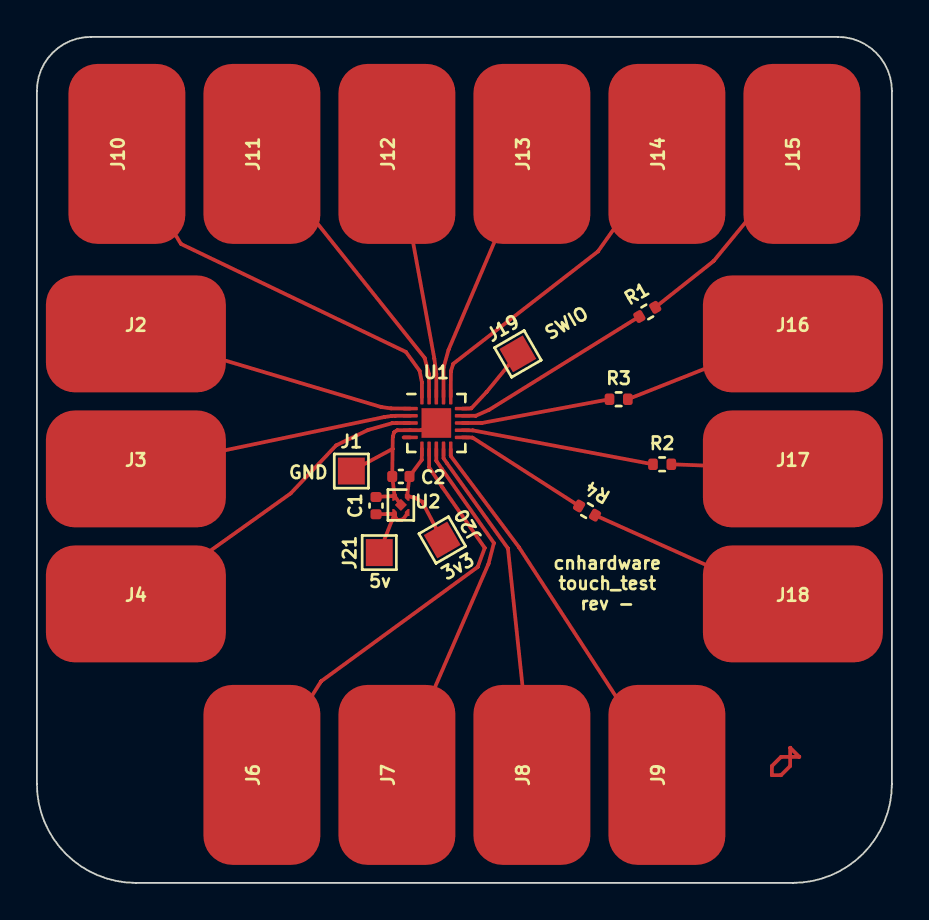
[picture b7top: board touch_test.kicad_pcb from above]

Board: 2 copper layers, 47.5 x 47.0 mm, 28 parts (0 on the bottom side), 24 nets.
